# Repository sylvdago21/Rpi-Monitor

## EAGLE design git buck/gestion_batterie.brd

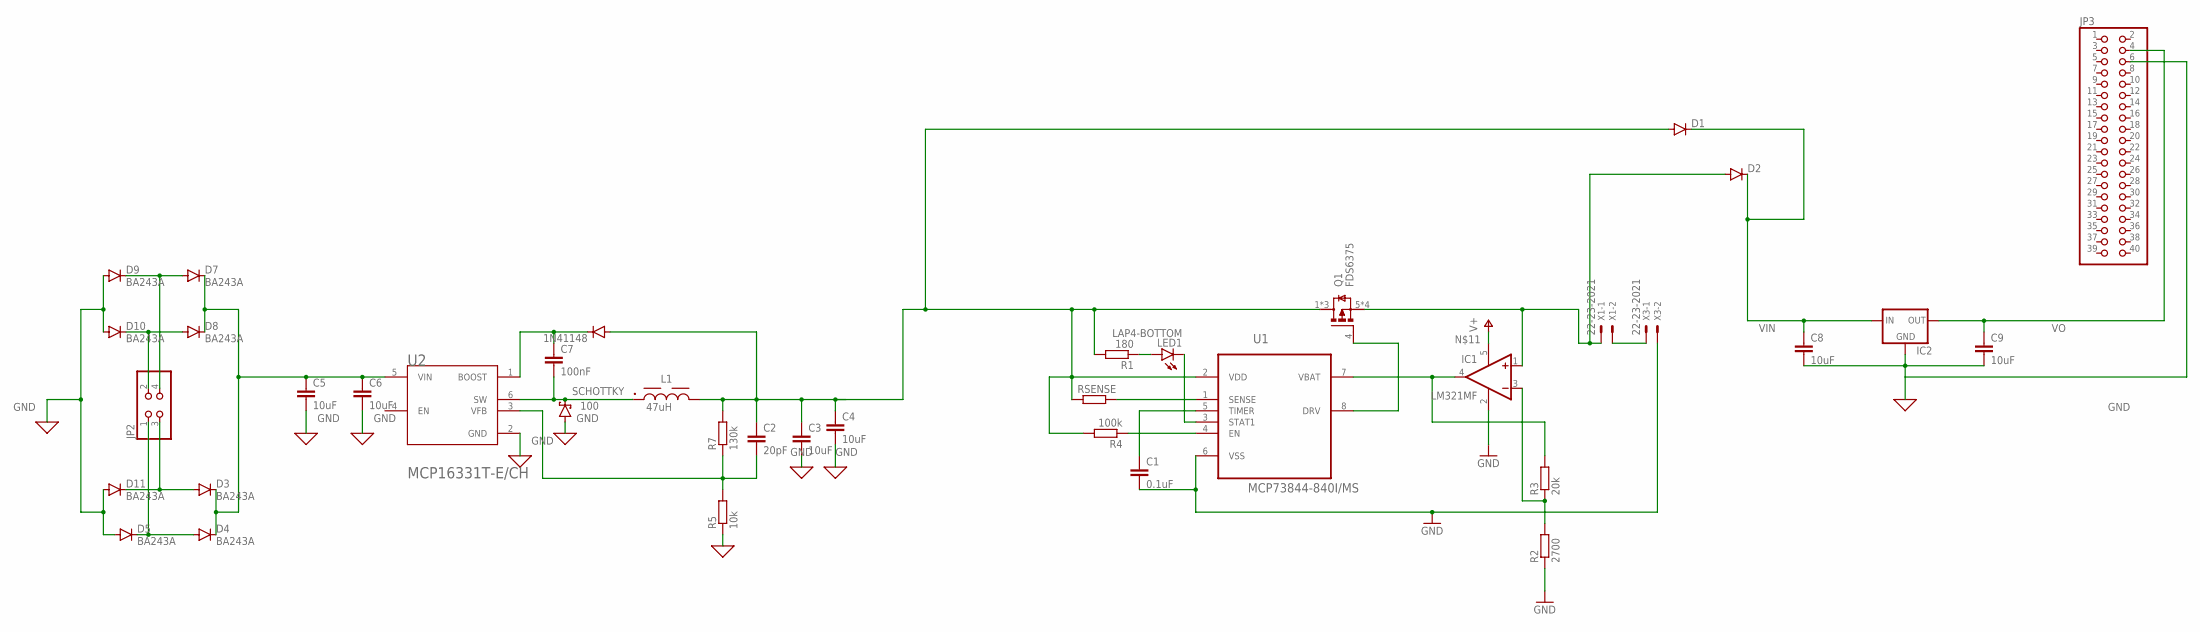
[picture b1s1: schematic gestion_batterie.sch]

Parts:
1N41148: DIODE-SOD323-W; SOD323-W
C1: 0.1uF; C1206
C2: 20pF; C1206
C3, C4, C5, C6, C8, C9: 10uF; C1206K
C7: 100nF; C1206
D1, D2: DIODE-DO201-15; DO201-15
D3, D4, D5, D7, D8, D9, D10, D11: BA243A; DO35-10
IC1: LM321MF; SOT23-5
IC2: 78MXXL
JP2: PINHD-2X2; 2X02
JP3: PINHD-2X20; 2X20
L1: 47uH; WE-PDA_1210
LED1: LAP4-BOTTOM; P47F-BOTTOM
Q1: FDS6375; SOIC127P600X175-8N
R1: 180; R1206
R2: 2700; R1206
R3: 20k; R1206
R4: 100k; R1206
R5: 10k; R1206
R7: 130k; R1206
RSENSE: R-EU_R1210; R1210
SCHOTTKY: 100; CB417-15
U1: MCP73844-840I/MS; SOP65P490X110-8N
U2: MICROCHIP_MCP16331T-E-CHMICROCHIP_MCP16331T-E-CH_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; MICROCHIP_MCP16331T-E-CH_0
X1, X3: 22-23-2021

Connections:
GND: C1.2, C3.2, C4.2, C5.2, C6.2, C8.2, C9.2, D5.A, D9.A, D10.A, D11.A, IC1.2 (V-), IC2.GND, JP3.6, R2.1, R5.1, SCHOTTKY.A, U1.6 (VSS), U2.2 (GND), X3.2
unnamed: RSENSE.2, U1.1 (SENSE)
unnamed: C1.1, U1.5 (TIMER)
unnamed: R4.1, U1.4 (EN)
unnamed: Q1.4 (G), U1.8 (DRV)
unnamed: IC1.4 (OUT), R3.2, U1.7 (VBAT)
unnamed: X1.2, X3.1
unnamed: LED1.A, R1.1
unnamed: D2.A, IC1.1 (+IN), Q1.5 (D), Q1.6 (D), Q1.7 (D), Q1.8 (D), X1.1
unnamed: IC1.3 (-IN), R2.2, R3.1
unnamed: LED1.C, U1.3 (STAT1)
unnamed: C5.1, C6.1, D3.C, D4.C, D7.C, D8.C, IC1.5 (V+), U2.5 (VIN)
unnamed: 1N41148.C, C7.1, U2.1 (BOOST)
unnamed: C7.2, L1.1, SCHOTTKY.C, U2.6 (SW)
unnamed: 1N41148.A, C2.1, C3.1, C4.1, D1.A, L1.2, Q1.1 (S), Q1.2 (S), Q1.3 (S), R1.2, R4.2, R7.2, RSENSE.1, U1.2 (VDD)
unnamed: C2.2, R5.2, R7.1, U2.3 (VFB)
unnamed: D3.A, D11.C, JP2.3
unnamed: D4.A, D5.C, JP2.1
unnamed: D8.A, D10.C, JP2.2
unnamed: D7.A, D9.C, JP2.4
VIN: C8.1, D1.C, D2.C, IC2.IN
VO: C9.1, IC2.OUT, JP3.4

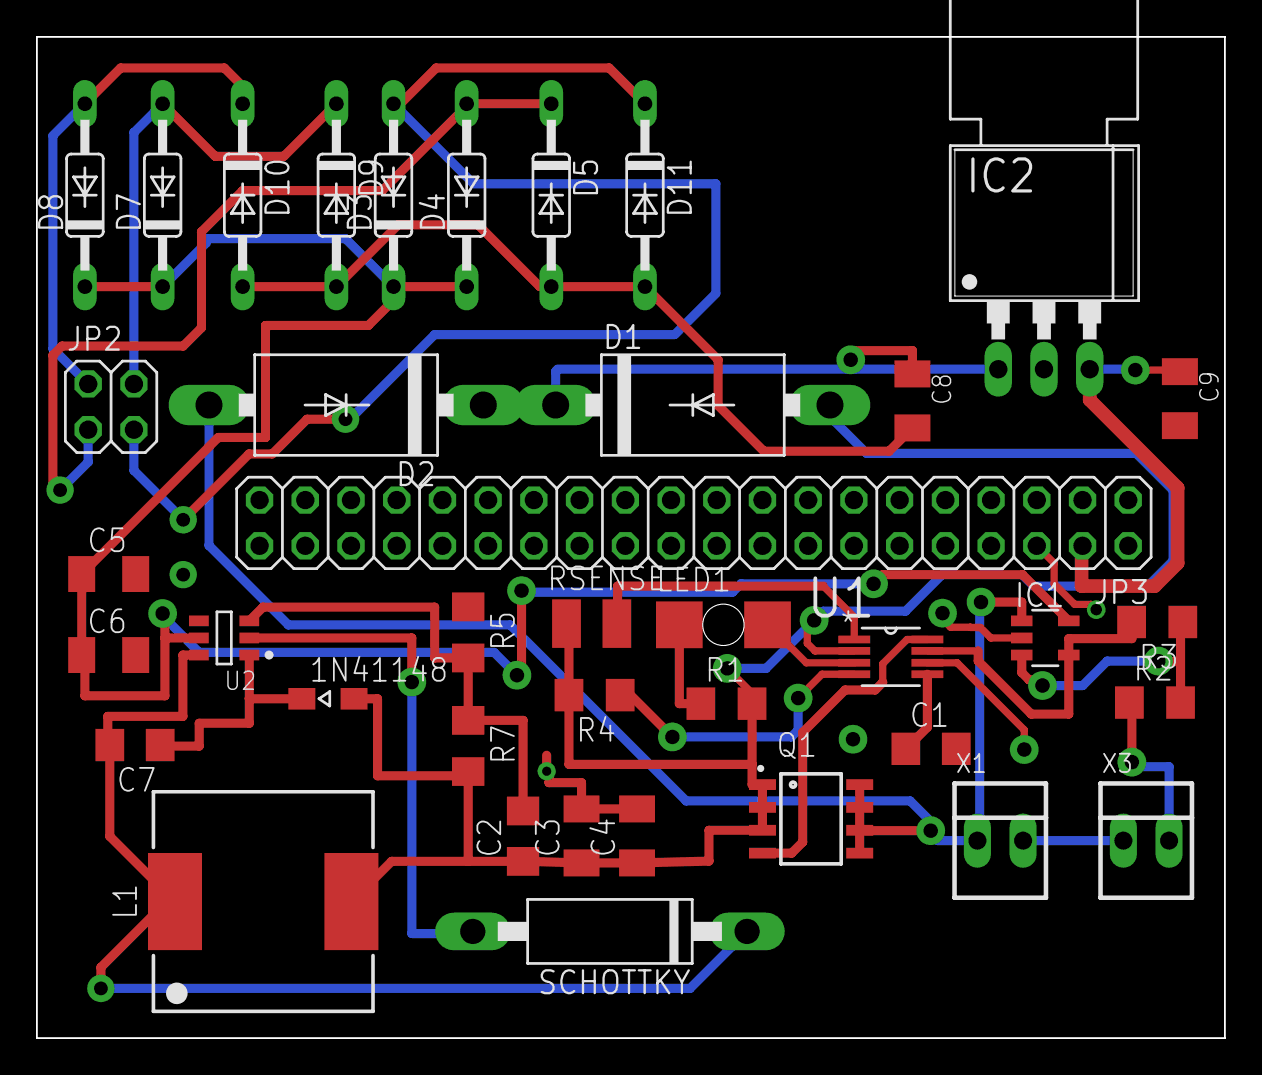
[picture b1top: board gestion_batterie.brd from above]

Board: 2 copper layers, 66.0 x 55.6 mm, 39 parts (0 on the bottom side), 22 nets.

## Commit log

2021-06-07 hello world
2021-06-07 message d'amour
2021-06-07 del test
2021-06-07 ajout des librairies eagle
2021-06-07 Datasheets
2021-06-07 suppr datasheet
2021-06-11 ajout documentation
2021-06-11 titre du projet
2021-06-13 Ajout doc buck ina
2021-06-14 Ajout derniers docs

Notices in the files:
parts and their libraries:
Eagle_WE-PDA: Copyright: Würth Elektronik
